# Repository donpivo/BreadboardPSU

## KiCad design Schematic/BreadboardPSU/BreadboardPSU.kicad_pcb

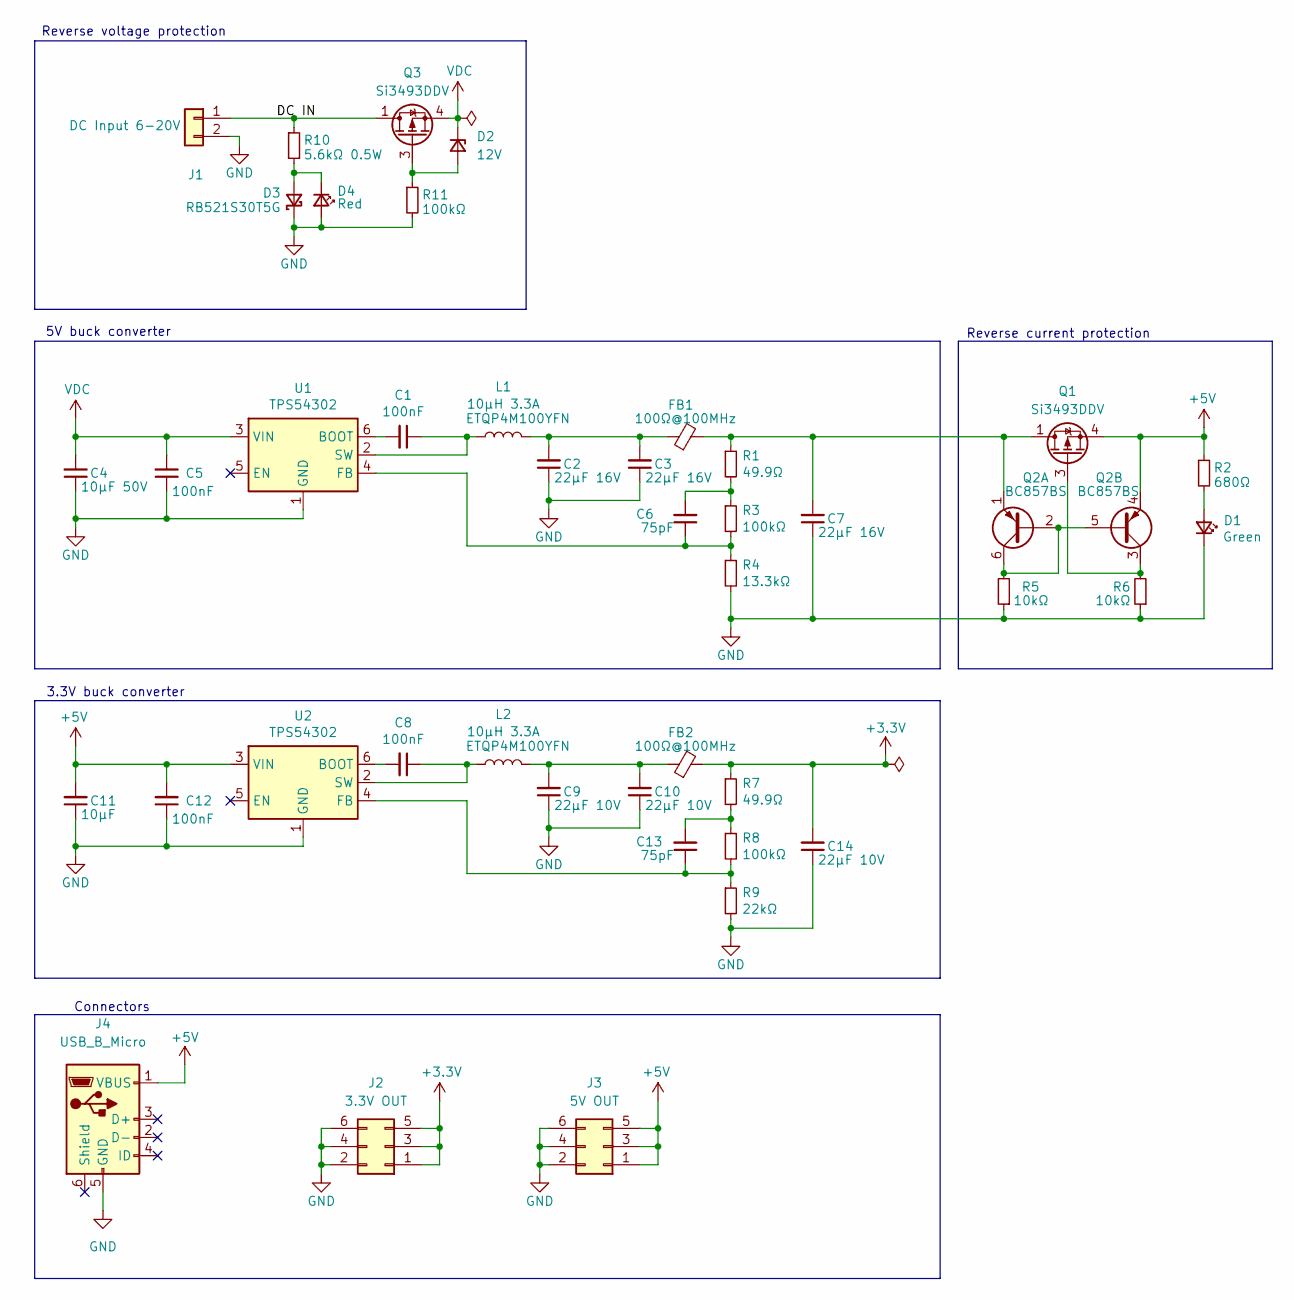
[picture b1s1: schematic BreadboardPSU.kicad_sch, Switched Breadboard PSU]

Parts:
C1, C5, C8, C12: 100nF; C_0603_1608Metric_Pad1.08x0.95mm_HandSolder
C2, C3, C7: 22µF 16V; C_0603_1608Metric_Pad1.08x0.95mm_HandSolder
C4: 10µF 50V; C_0805_2012Metric_Pad1.18x1.45mm_HandSolder
C6, C13: 75pF; C_0603_1608Metric_Pad1.08x0.95mm_HandSolder
C9, C10, C14: 22µF 10V; C_0603_1608Metric_Pad1.08x0.95mm_HandSolder
C11: 10µF; C_0603_1608Metric_Pad1.08x0.95mm_HandSolder
D1: Green; LED_0603_1608Metric_Pad1.05x0.95mm_HandSolder
D2: 12V; D_SOD-523
D3: RB521S30T5G; D_SOD-523
D4: Red; LED_0603_1608Metric_Pad1.05x0.95mm_HandSolder
FB1, FB2: 100Ω@100MHz; L_1206_3216Metric_Pad1.42x1.75mm_HandSolder
J1: DC Input 6-20V; Pluggable_DB2ERC-5.08-2P-BK
J2: 3.3V OUT; PinHeader_2x03_P2.54mm_Vertical_Alt
J3: 5V OUT; PinHeader_2x03_P2.54mm_Vertical_Alt
J4: USB_B_Micro; USB_Micro_B_Female_10118194-0001LF
L1, L2: 10µH 3.3A; ETQP4M100YFN
Q1, Q3: Si3493DDV; SOT-23-6_Handsoldering
Q2: BC857BS; SOT-363_SC-70-6-Handsoldering
R1, R7: 49.9Ω; R_0603_1608Metric_Pad0.98x0.95mm_HandSolder
R2: 680Ω; R_0603_1608Metric_Pad0.98x0.95mm_HandSolder
R3, R8, R11: 100kΩ; R_0603_1608Metric_Pad0.98x0.95mm_HandSolder
R4: 13.3kΩ; R_0603_1608Metric_Pad0.98x0.95mm_HandSolder
R5, R6: 10kΩ; R_0603_1608Metric_Pad0.98x0.95mm_HandSolder
R9: 22kΩ; R_0603_1608Metric_Pad0.98x0.95mm_HandSolder
R10: 5.6kΩ 0.5W; R_1210_3225Metric_Pad1.30x2.65mm_HandSolder
U1, U2: TPS54302; SOT-23-6_Handsoldering

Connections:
+3.3V: C14.2, FB2.2, J2.1, J2.3, J2.5, R7.1
+5V: C11.2, C12.2, J3.1, J3.3, J3.5, J4.1 (VBUS), Q1.4 (S), Q2.4 (E2), R2.1, U2.3 (VIN)
/DC IN: J1.1, Q3.1 (D), Q3.2 (D), Q3.5 (D), Q3.6 (D), R10.1
GND: C2.1, C3.1, C4.1, C5.1, C7.1, C9.1, C10.1, C11.1, C12.1, C14.1, D1.1 (K), D3.1 (K), D4.2 (A), J1.2, J2.2, J2.4, J2.6, J3.2, J3.4, J3.6, J4.5 (GND), R4.2, R5.1, R6.1, R9.2, R11.2, U1.1 (GND), U2.1 (GND)
unnamed: C2.2, C3.2, FB1.1, L1.2
unnamed: C6.2, R1.2, R3.1
unnamed: C9.2, C10.2, FB2.1, L2.2
unnamed: C13.2, R7.2, R8.1
unnamed: D1.2 (A), R2.2
unnamed: D2.2 (A), Q3.3 (G), R11.1
unnamed: D3.2 (A), D4.1 (K), R10.2
unnamed: Q1.3 (G), Q2.3 (C2), R6.2
unnamed: Q2.2 (B1), Q2.5 (B2), Q2.6 (C1), R5.2
unnamed: C7.2, FB1.2, Q1.1 (D), Q1.2 (D), Q1.5 (D), Q1.6 (D), Q2.1 (E1), R1.1
unnamed: C1.2, U1.6 (BOOT)
unnamed: C6.1, R3.2, R4.1, U1.4 (FB)
unnamed: C1.1, L1.1, U1.2 (SW)
unnamed: C8.2, U2.6 (BOOT)
unnamed: C13.1, R8.2, R9.1, U2.4 (FB)
unnamed: C8.1, L2.1, U2.2 (SW)
VDC: C4.2, C5.2, D2.1 (K), Q3.4 (S), U1.3 (VIN)

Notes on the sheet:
5V buck converter
Connectors
Reverse current protection
3.3V buck converter
Reverse voltage protection

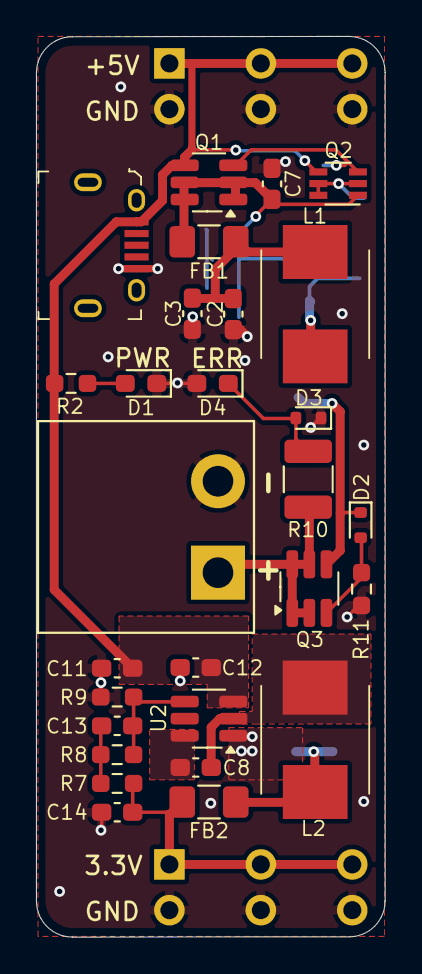
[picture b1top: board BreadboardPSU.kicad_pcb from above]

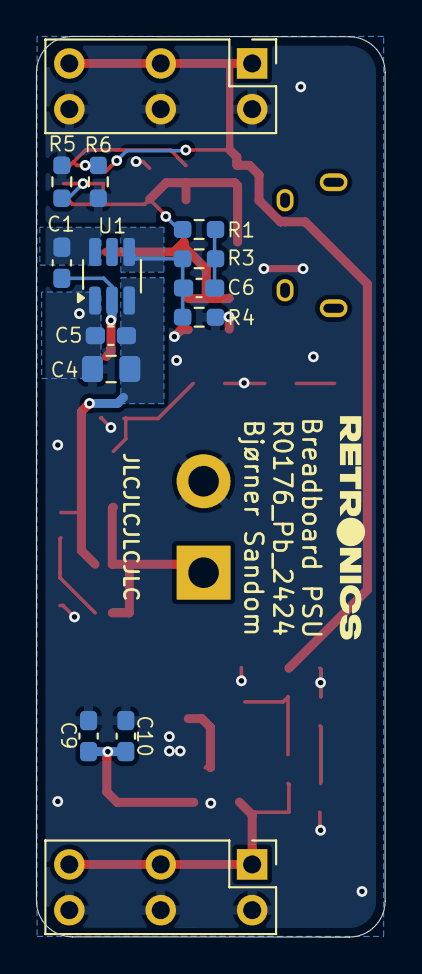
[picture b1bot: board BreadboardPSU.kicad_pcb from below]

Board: 2 copper layers, 19.4 x 50.0 mm, 42 parts (14 on the bottom side), 21 nets.

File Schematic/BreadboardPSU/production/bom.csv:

Designator,Footprint,Quantity,Value,LCSC Part #
"C1, C12, C5, C8",0603,4,100nF,
"C10, C14, C2, C3, C7, C9",0603,6,22µF 10V,
C11,0603,1,10µF,
"C13, C6",0603,2,75pF,
C4,0805,1,10µF 50V,
D1,0603,1,Green,
D2,D_SOD-523,1,12V,
D3,D_SOD-523,1,RB521S30T5G,
D4,0603,1,Red,
"FB1, FB2",1206,2,100Ω@100MHz,
J1,Pluggable_DB2ERC-5.08-2P-BK,1,DC Input 6-24V,
J2,PinHeader_2x03_P2.54mm_Vertical_Alt,1,3.3V OUT,
J3,PinHeader_2x03_P2.54mm_Vertical_Alt,1,5V OUT,
J4,USB_Micro_B_Female_10118194-0001LF,1,USB_B_Micro,
"L1, L2",ETQP4M100YFN,2,10µH 3.3A,
"Q1, Q3",SOT-23-6_Handsoldering,2,Si3493DDV,
Q2,SOT-363_SC-70-6-Handsoldering,1,BC857BS,
"R1, R7",0603,2,49.9Ω,
R10,1210,1,5.6kΩ 0.5W,
"R11, R2, R3, R8",0603,4,100kΩ,
R4,0603,1,13.3kΩ,
"R5, R6",0603,2,10kΩ,
R9,0603,1,22kΩ,
"U1, U2",SOT-23-6_Handsoldering,2,TPS54302,
